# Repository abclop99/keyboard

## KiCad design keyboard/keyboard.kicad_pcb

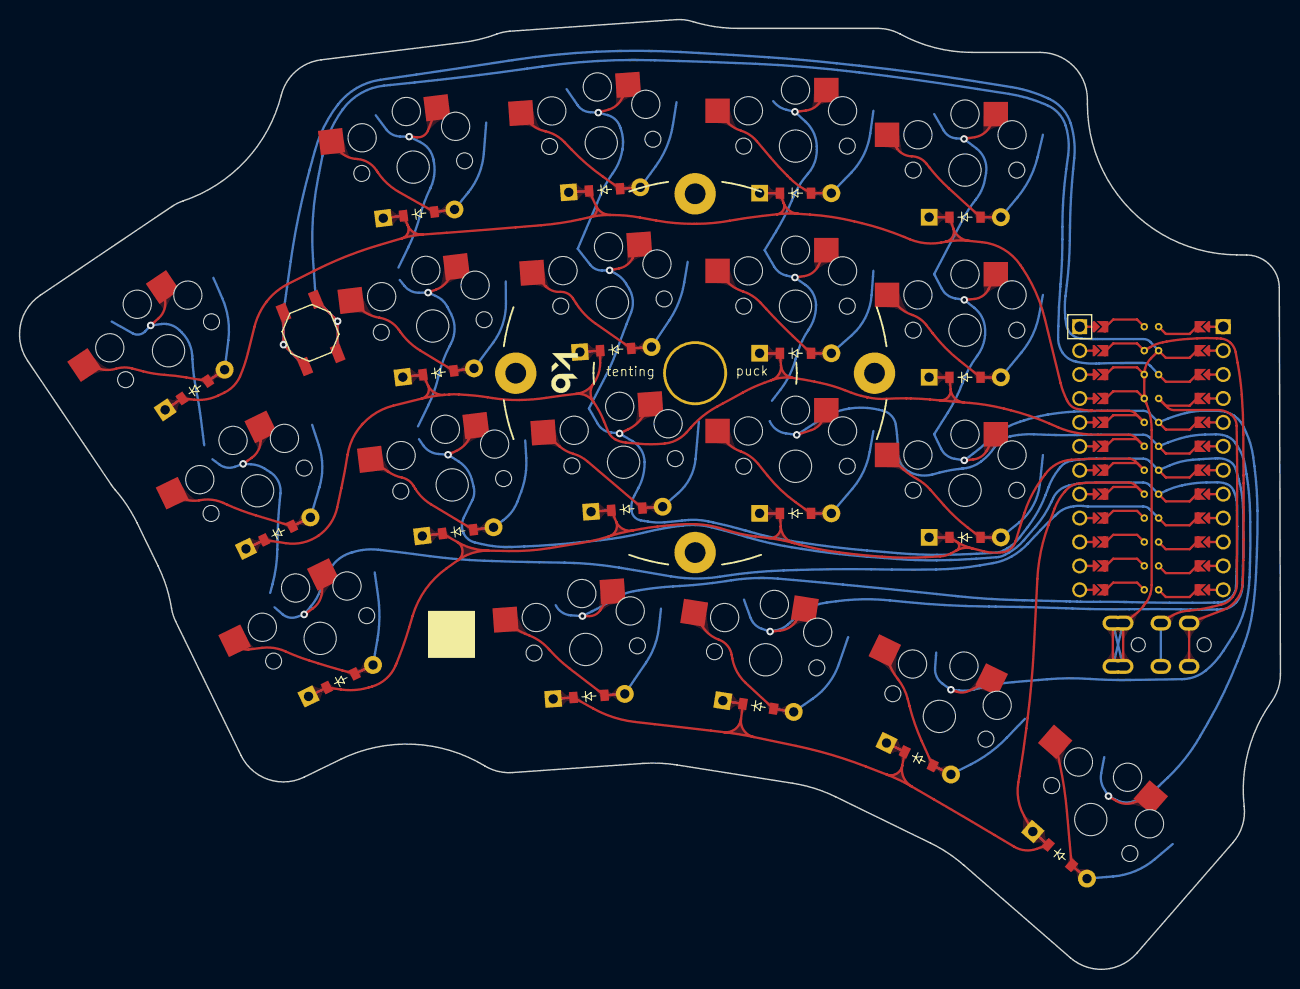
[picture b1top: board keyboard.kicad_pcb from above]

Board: 2 copper layers, 133.9 x 100.9 mm, 42 parts (0 on the bottom side), 32 nets.

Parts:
B1, B2: SW_TACT_ALPS_SKQGABE010
D1, D2, D3, D4, D5, D6, D7, D8, D9, D10, D11, D12, D13, D14, D15, D16, D17, D18, D19: ComboDiode
S1, S2, S3, S4, S5, S6, S7, S8, S9, S10, S11, S12, S13, S14, S15, S16, S17, S18, S19: PG1350
TRRS1: TRRS-PJ-320A-dual
_1: ProMicro

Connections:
B1: S1.1, S2.1, S3.1, _1.9
C6: D16.1, D17.1, D18.1, D19.1, _1.17
D0: D2.1, D5.1, D8.1, D11.1, D14.1, _1.19
D1: D3.1, D6.1, D9.1, D12.1, D15.1, _1.20
D2: TRRS1.4, _1.23
D4: D1.1, D4.1, D7.1, D10.1, D13.1, _1.18
F4: S13.1, S14.1, S15.1, S19.1, _1.5
F5: S10.1, S11.1, S12.1, S18.1, _1.6
F6: S7.1, S8.1, S9.1, S17.1, _1.7
F7: S4.1, S5.1, S6.1, S16.1, _1.8
GND: B1.1, B2.1, TRRS1.1, TRRS1.2, _1.2, _1.21, _1.22
RST: B1.2, B2.2, _1.3
VCC: TRRS1.3, _1.4
extra_tucky_thumb: D16.2, S16.2
far_bottom: D13.2, S13.2
far_home: D14.2, S14.2
far_top: D15.2, S15.2
index_bottom: D10.2, S10.2
index_home: D11.2, S11.2
index_top: D12.2, S12.2
middle_bottom: D7.2, S7.2
middle_home: D8.2, S8.2
middle_top: D9.2, S9.2
pinkie_bottom: D1.2, S1.2
pinkie_home: D2.2, S2.2
pinkie_top: D3.2, S3.2
reachy_thumb: D19.2, S19.2
resty_thumb: D18.2, S18.2
ring_bottom: D4.2, S4.2
ring_home: D5.2, S5.2
ring_top: D6.2, S6.2
tucky_thumb: D17.2, S17.2

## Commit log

2024-04-07 Add layout config
2024-04-07 Add a scanned image of the WIP layout
2024-04-07 Add package-lock and keycaps.blend
2024-04-07 Swap to promicro_pretty
2024-04-08 Add the pcb stuff???
2024-04-08 Fix wrong connections
2024-04-08 Route top row non-pinkie
2024-04-08 Route non-pinkie home row
2024-04-08 Clean up some stuff
2024-04-08 Connect the rest of the stuff
2024-04-08 Fix some things
2024-04-08 Add teardrops
2024-04-08 Tent puck and some cleanup
2024-04-08 Fix a few issues
    A clearance issue, and the reset pads on the opposite sides not
    connected to each other.
2024-04-09 Add rounded version with JLC order number placeholder
2024-08-09 Remake keyboard
    It seems like there is some problem with the kicad project now
2024-08-09 Fix kicad project
2024-08-09 Fix reset button orientation
    For easier and prettier routing
2024-08-10 Add connections on PCB
2024-08-10 Add a rounded version
2024-08-10 Fix some DRC issues in rounded PCB
2024-08-11 Fix a wrong connection on MCU, rewire PCB
2024-08-12 Re-route traces a to look more organic
2024-08-16 Add an extra thumb key (extra tucky)
2024-08-17 Fill in unfilled zone, tweak curve
2024-08-18 Add tenting puck, reroute traces around
2024-09-01 Change JLC order number position to barcode position
